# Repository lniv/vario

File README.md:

# vario

A sailplane / soaring  variometer project.
Minimal use is as a standalone vario, using a pressure sensor (typically connected to a TE probe) to measure climb rate. The code running on a teensy 3.1  (using the teensyduino environment (but not the IDE (shudder)) drives an indicator gauge stepper and a speaker.
Optionally, a differential pressure sensor and a gps are connected to the uC, and information is sent to a flight computer.
Current protocol implemented is the open vario one, and the gps GPRMC sentences are just echoed.
Currently a 9dof imu is connected as well, but the data is not procssed. In the far future one could integrate barometric / imu / gps data to get a better state estimate.

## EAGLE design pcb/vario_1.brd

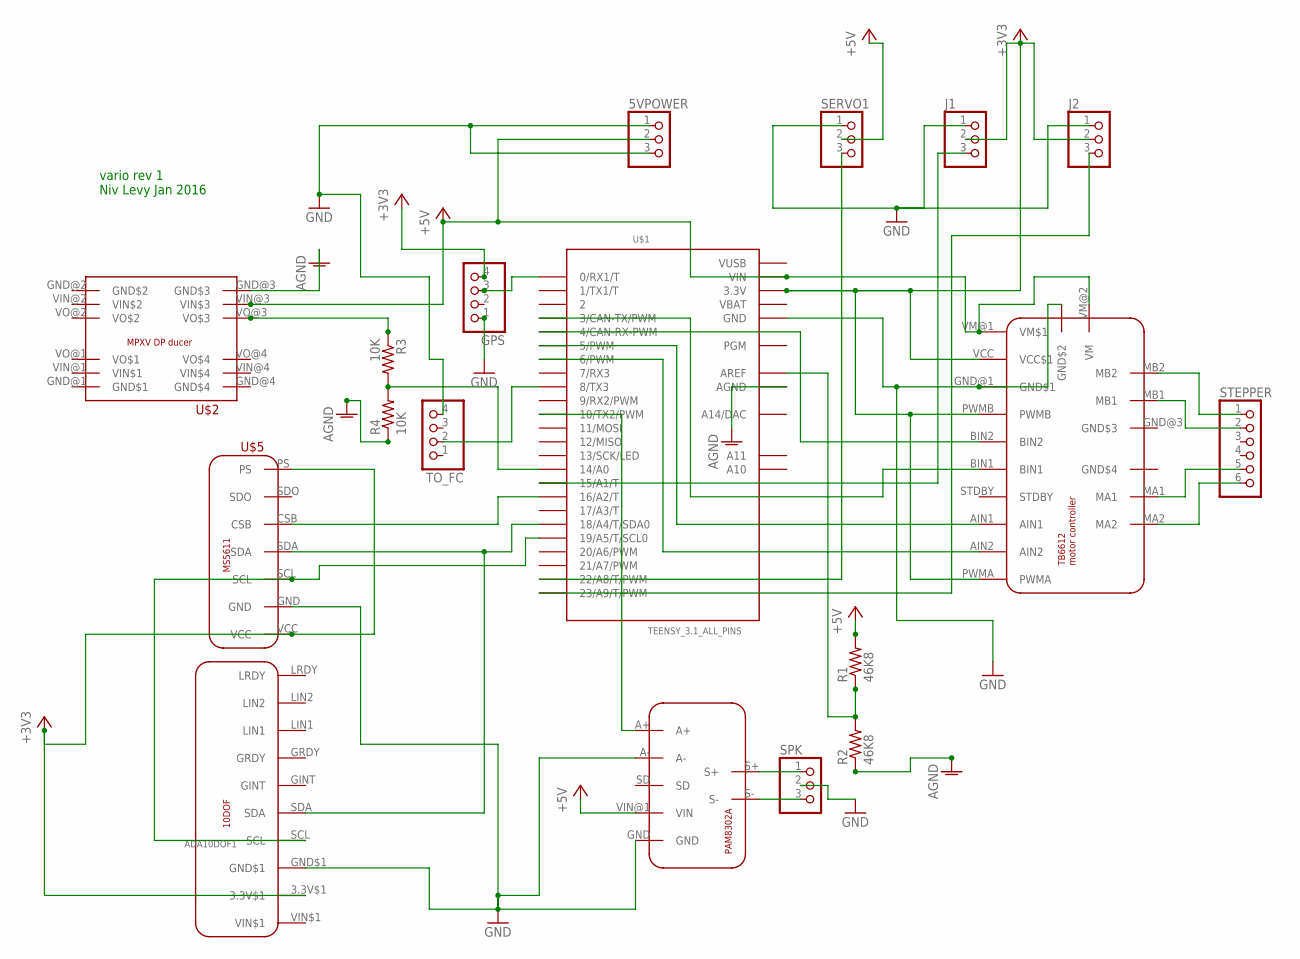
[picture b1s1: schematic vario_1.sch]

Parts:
5VPOWER: PINHD-1X3; 1X03
ADA10DOF1: 10DOF_BREAKOUT; 10_DOF_BREAKOUT
GPS: PINHD-1X4; 1X04
J1, J2: PINHD-1X3; 1X03
R1, R2: 46K8; 0207/10
R3, R4: 10K; 0207/10
SERVO1: PINHD-1X3; 1X03
SPK: PINHD-1X3; 1X03
STEPPER: PINHD-1X6; 1X06
TO_FC: PINHD-1X4; 1X04
U$1: TEENSY_3.1_ALL_PINS; TEENSY3-ALL_PINS
U$2: MPXV
U$3: TB6612_BREAKOUT
U$4: PAM8302A_BREAKOUT
U$5: MS5611_BREAKOUT

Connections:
+3V3: ADA10DOF1.3.3V$1, GPS.4, J1.2, J2.2, U$1.3.3V, U$1.3.3V1 (3.3V), U$3.PWMA, U$3.PWMB, U$3.VCC (VCC$1), U$5.PS, U$5.VCC
+5V: 5VPOWER.2, R1.2, SERVO1.2, U$1.VIN, U$2.VIN@3 (VIN$3), U$3.VM@1 (VM$1), U$3.VM@2 (VM), U$4.VIN@1 (VIN)
AGND: R2.1, R4.1, U$1.AGND, U$2.GND@3 (GND$3)
GND: 5VPOWER.1, 5VPOWER.3, ADA10DOF1.GND$1, GPS.1, J1.1, J2.1, SERVO1.1, SPK.2, TO_FC.4, U$1.GND, U$1.GND1 (GND), U$3.GND@1 (GND$1), U$3.GND@2 (GND$2), U$4.A-, U$4.GND, U$5.GND
unnamed: STEPPER.1, U$3.MB2
unnamed: STEPPER.2, U$3.MB1
unnamed: STEPPER.6, U$3.MA2
unnamed: STEPPER.5, U$3.MA1
unnamed: U$1.16/A2 (16/A2/T), U$5.CSB
unnamed: U$1.6 (6/PWM), U$3.AIN2
unnamed: U$1.5 (5/PWM), U$3.AIN1
unnamed: U$1.4 (4/CAN-RX-PWM), U$3.BIN2
unnamed: U$1.3 (3/CAN-TX/PWM), U$3.BIN1
unnamed: ADA10DOF1.SDA, U$1.18/A4 (18/A4/T/SDA0), U$5.SDA
unnamed: ADA10DOF1.SCL, U$1.19/A5 (19/A5/T/SCL0), U$5.SCL
unnamed: R3.2, R4.2, U$1.14/A0
unnamed: R1.1, R2.2, U$1.AREF
unnamed: R3.1, U$2.VO@3 (VO$3)
unnamed: TO_FC.2, U$1.8 (8/TX3)
unnamed: U$1.10 (10/TX2/PWM), U$4.A+
unnamed: GPS.3, U$1.0 (0/RX1/T)
unnamed: SPK.1, U$4.S+
unnamed: J1.3, U$1.15/A1 (15/A1/T)
unnamed: SERVO1.3, U$1.22/A8 (22/A8/T/PWM)
unnamed: J2.3, U$1.23/A9 (23/A9/T/PWM)
unnamed: SPK.3, U$4.S-
VBAT: U$1.VBAT
VUSB: U$1.VUSB

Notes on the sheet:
vario rev 1 Niv Levy Jan 2016

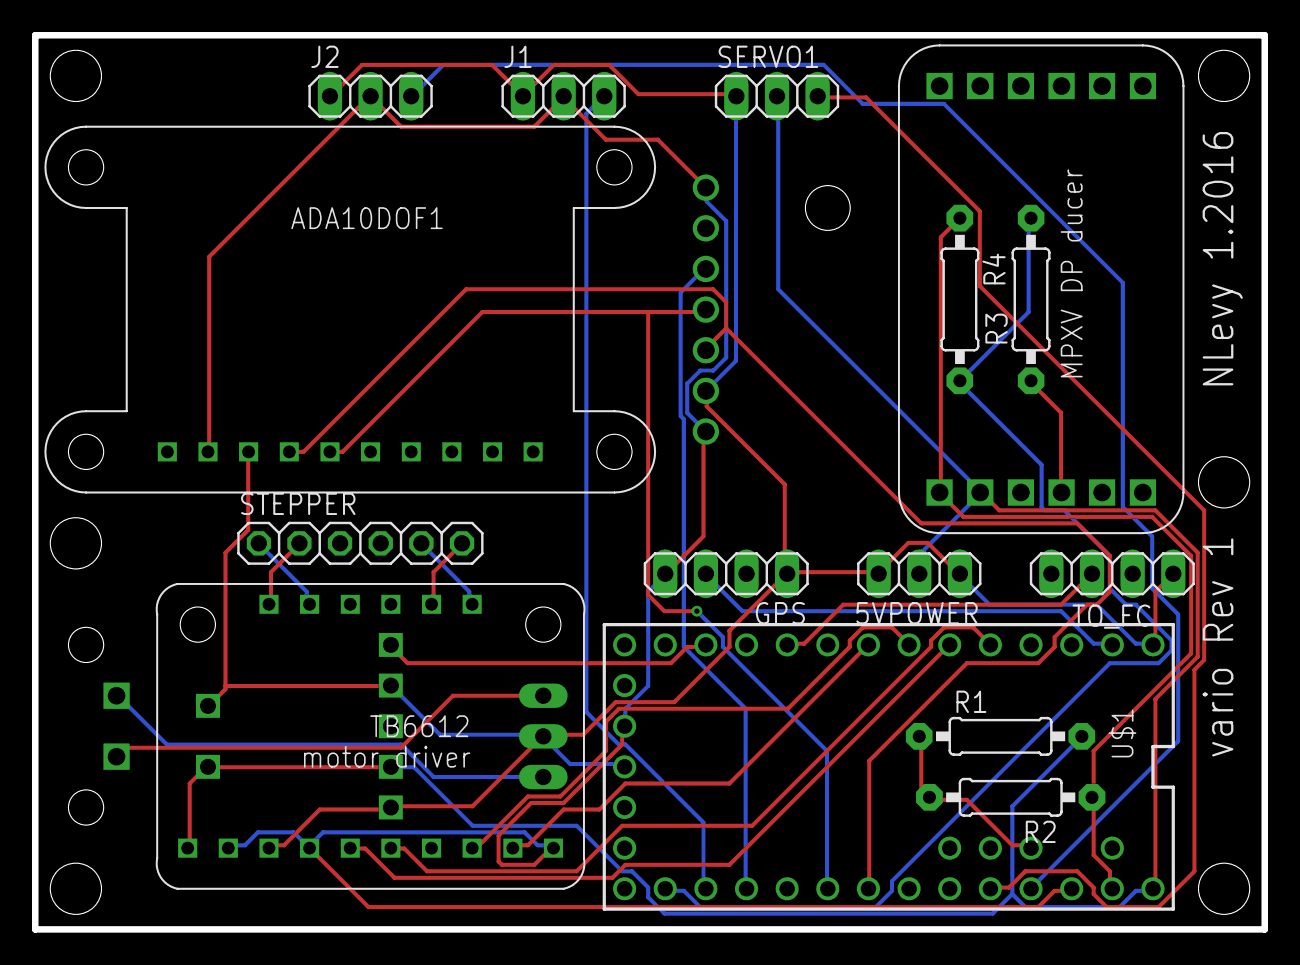
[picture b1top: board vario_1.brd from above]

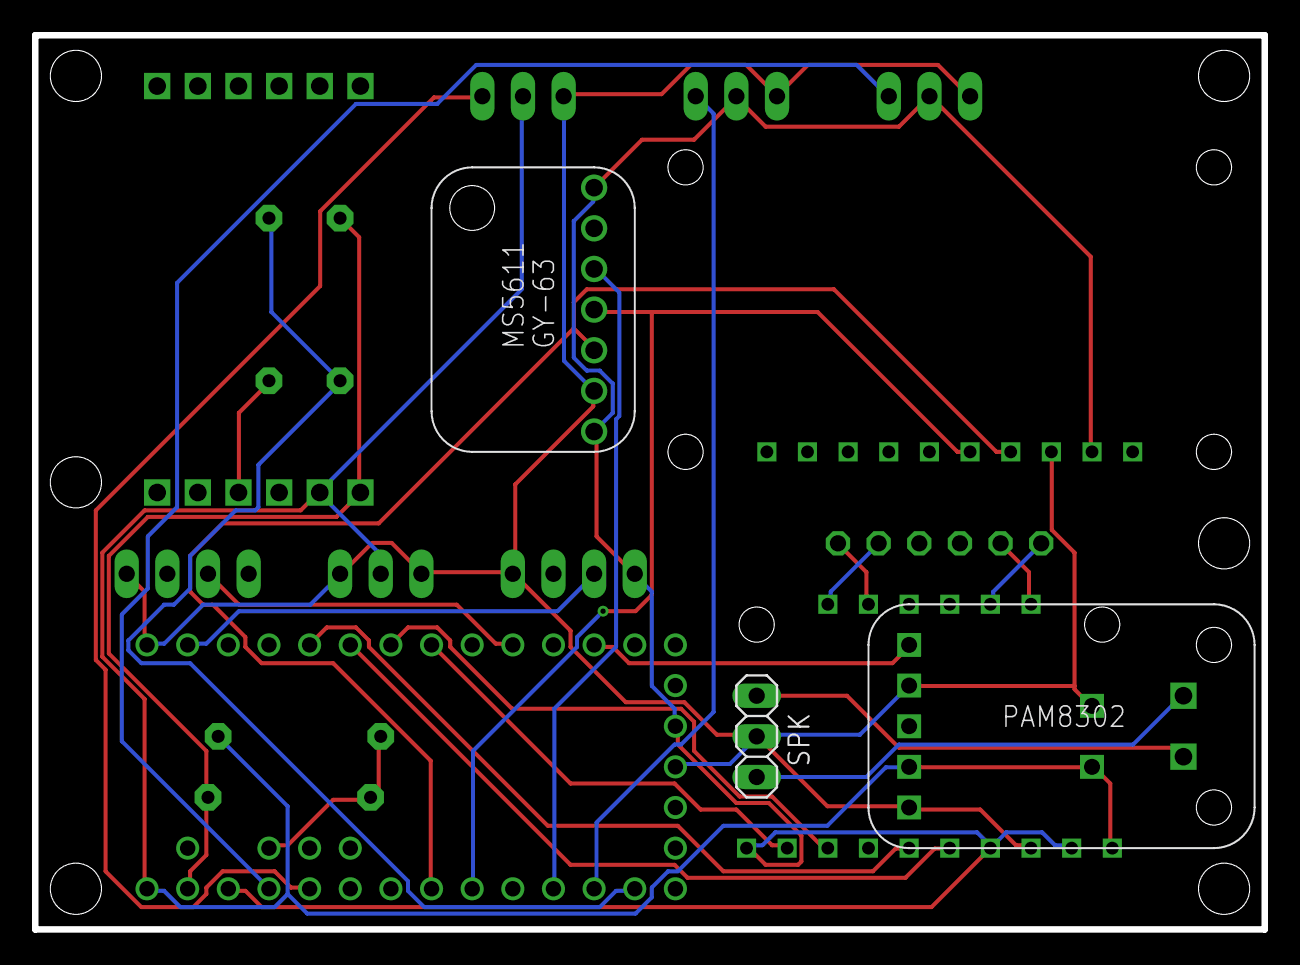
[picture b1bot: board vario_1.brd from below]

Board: 2 copper layers, 76.8 x 55.9 mm, 18 parts (3 on the bottom side), 26 nets.

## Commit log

2015-07-12 Initial commit - simple audio and steeper needle baed vario.
2015-07-12 added minimal license file
2015-07-13 Replaced linear regression of heights with a (sort of) proper iir bessel filter that i got from filtduino. Does seem to behave somewhat better.
2015-07-13 Replaced the variable chopping with a fixed one (could never get it to sound nice) back to a single pole iir filter, seems stable stepper is now consistent and matches climb rate. it might be worthwh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
2015-07-13 Added a BOM
2015-07-14 Added minimal gps code - not doing anythin with it yet.
2015-07-18 minimal adc code to read a diff pressure sensor (MXPV7007DP) connected to the teensy (not doing anything with it beyond logging to serial)
2015-07-18 using a 4th order butterworth - much quieter
2015-07-18 added airspeed calculation. filtered the same as the vario. despite trying to get a sensor offset at start, seems to gather an offset later and stabilize at a few m/sec offset.
2015-07-19 Calculate airspeed and send airspeed, pressure and vario to FC using openvario protocol - which i'm not sure if working (or maybe somehting else is wrong). In any case, i can connect to the nook and 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
2015-07-19 Added a pseudo schematic - done in inkscape in a lego block style, to match overall project.
2015-07-19 updated description
2015-11-23 Added a MS-5611 module and code to drive it (and corrected schematics, BOM to match). A define statment chooses between using it and the BMP180 as the pressure sources. Also corrected a scaling for v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
2015-11-29 adding a first revision of mechanicals; i have printed the three files attached and assembled (using a 3" od. x 1/8" wall acrylic tube as the body) However, the rear piece is more of a place holder -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
2015-11-29 adding assembly
2015-11-30 fixed an extra carriage return which was breaking communication with recent TopHat / xcsoar - at some point the generic nema parsing became stricter.
2015-12-01 minor cleanup of comments
2015-12-27 airspeed: changed TAS calculation, using a the first N readings to establish a baseline - currently starting in flight would be bad. changed ADC to use a 1:1 splitter on the 5V supply as the referenc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
2015-12-27 code cleanup, no functional change
2016-02-18 Changed baudrate to match that of a ESP8266 acting as a serial to wifi bridge, transmitting each message upon newline (instead of going directly to the flight computer). the code for the ESP8266 adde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
2016-02-18 Adding eagle files for a pcb - this acts mostly as a minimal repalcement for breadboarding the setup. It doesn't have e.g. decoupling caps or really much else beyond replacing the wire tangle. Note t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
2016-09-07 * replaced single iir filter with three cascaded sos; not really working well, and only used here for climb rate * replaced modulu with zeroing of counter * fixed initialization to use MS5611 or bmp,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
2016-09-07 Replaced iir with simple running average, taken from http://playground.arduino.cc/Main/RunningAverage aka https://github.com/RobTillaart/Arduino/tree/master/libraries/RunningAverage Set period to 1se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
2016-09-07 Add an offset to the stepper to fine tune the neutral position. (but stepper motion is off here)
2016-09-07 Turned on actual stepper motion (and corrected a small typo in setting midpoint)
2016-09-08 properly cascading second orde section. adhoc divided stepper multiplier by 10 - at least it's quieter. trying to fill the filter with a fixed value as starting point - not working well.
2016-09-08 constraining climb rate to +-30 m/sec as an adhoc sanity constraint.
2018-02-05 no real change to code, moving the teensy code to its own folder, as necessary for arduino to compile
2018-02-05 Played with filters - a 0.25 Hz 4th order bessel has low enough ringing that it might be useable. also added some printouts and a (too long) averaging loop around the initial alittude fill - but it's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
2018-02-05 Seems i was applying the sos in the wrong order; fixed, i think. also was not initializing X in the filters. made length of initial averaging dependent on a define - set to 20, 100 it too much, but 2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
